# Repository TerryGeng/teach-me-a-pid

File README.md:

# teach-me-a-pid
Simplified schematic of a PID controller

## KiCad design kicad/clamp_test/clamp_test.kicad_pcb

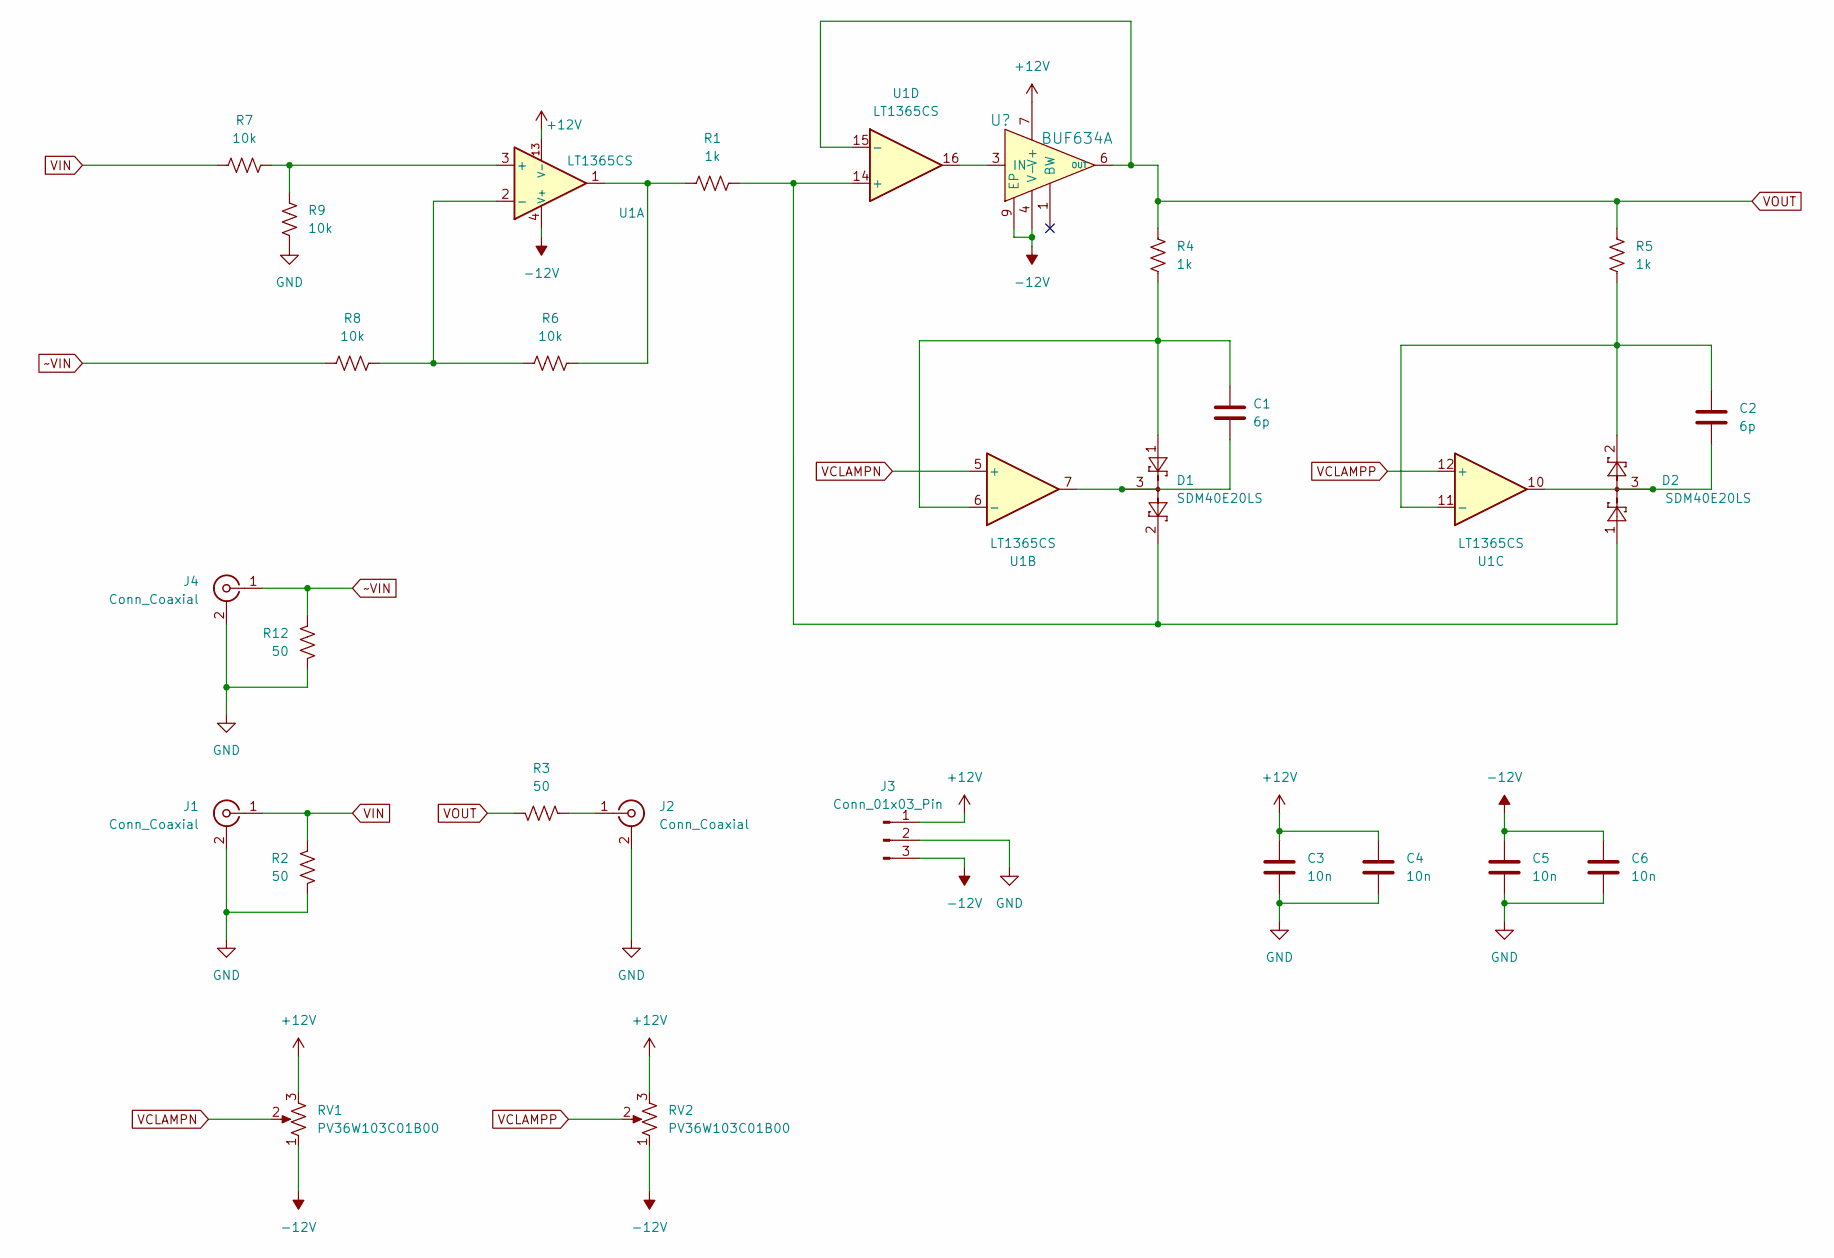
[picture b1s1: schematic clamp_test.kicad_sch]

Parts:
C1, C2: 6p; C_0603_1608Metric
C3, C4, C5, C6: 10n; C_0603_1608Metric
D1, D2: SDM40E20LS; SOT-23
J1, J2, J4: Conn_Coaxial; SMA_Amphenol_132291_Vertical
J3: Conn_01x03_Pin; PinHeader_1x03_P2.54mm_Vertical
R1, R4, R5: 1k; R_0603_1608Metric
R2, R3, R12: 50; R_0603_1608Metric
R6, R7, R8, R9: 10k; R_0603_1608Metric
RV1, RV2: PV36W103C01B00; Potentiometer_Bourns_3296W_Vertical
U1: LT1365CS; SOIC-16_3.9x9.9mm_P1.27mm
U2: BUF634A; TI_SO-PowerPAD-8_ThermalVias; PARTNO BUF634AIDDAR; DIGIKEY 296-BUF634AIDDARCT-ND

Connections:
+12V: C3.1, C4.1, J3.1, RV1.3, RV2.3, U1.13 (V-), U2.7 (V+)
-12V: C5.1, C6.1, J3.3, RV1.1, RV2.1, U1.4 (V+), U2.4 (V-), U2.9 (EP)
GND: C3.2, C4.2, C5.2, C6.2, J1.2 (Ext), J2.2 (Ext), J3.2, J4.2 (Ext), R2.2, R9.2, R12.2
unnamed: C1.2, D1.3, U1.7
unnamed: C2.2, D2.3, U1.10
unnamed: J2.1 (In), R3.2
unnamed: R1.1, R6.1, U1.1
unnamed: R7.1, R9.1, U1.3 (+)
unnamed: R6.2, R8.1, U1.2 (-)
unnamed: C1.1, D1.1, R4.1, U1.6 (-)
unnamed: C2.1, D2.2, R5.1, U1.11 (-)
unnamed: D1.2, D2.1, R1.2, U1.14 (+)
unnamed: U1.16, U2.3 (IN)
VCLAMPN: RV1.2, U1.5 (+)
VCLAMPP: RV2.2, U1.12 (+)
VIN: J1.1 (In), R2.1, R7.2
VOUT: R3.1, R4.2, R5.2, U1.15 (-), U2.6 (OUT)
~VIN: J4.1 (In), R8.2, R12.1

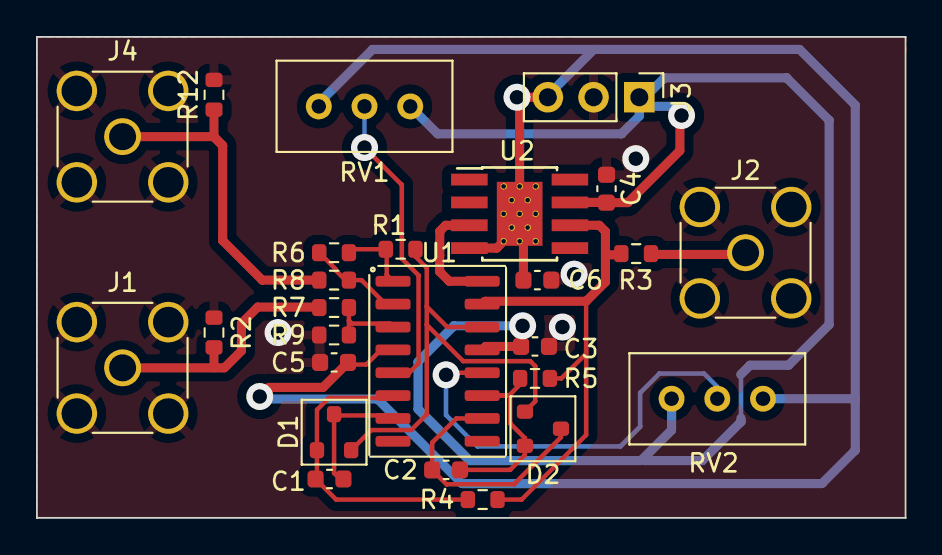
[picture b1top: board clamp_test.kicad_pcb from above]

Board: 2 copper layers, 48.3 x 26.7 mm, 26 parts (0 on the bottom side), 18 nets.

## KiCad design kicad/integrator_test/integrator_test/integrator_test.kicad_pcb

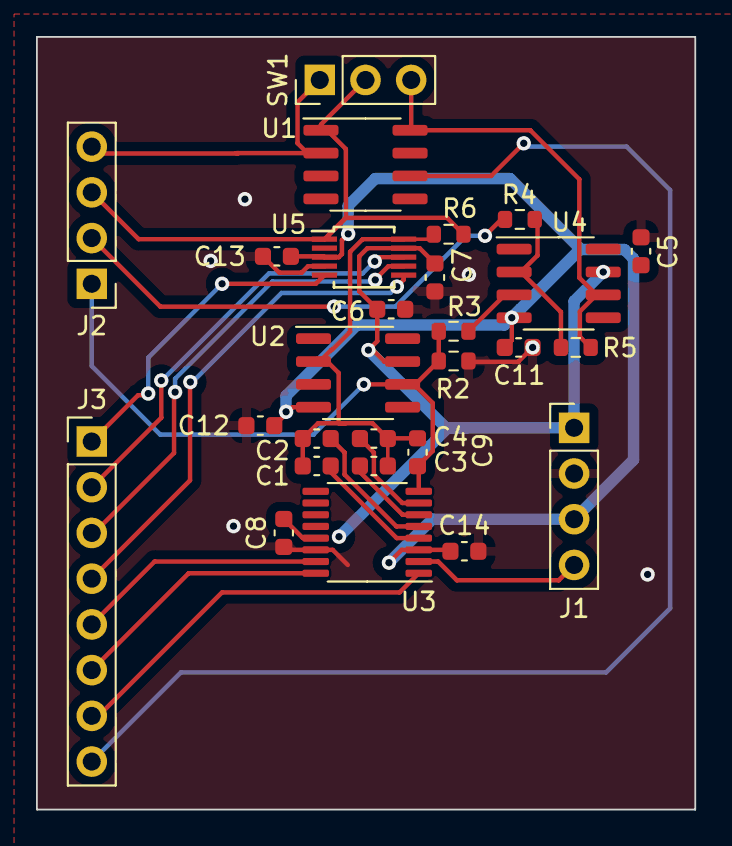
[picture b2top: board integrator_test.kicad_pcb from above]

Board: 2 copper layers, 36.6 x 42.9 mm, 27 parts (0 on the bottom side), 24 nets.

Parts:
C1: 1nF; C_0603_1608Metric
C2: 10nF; C_0603_1608Metric
C3, C5, C6, C7, C8, C11, C12, C13, C14: 100nF; C_0603_1608Metric
C4: 1uF; C_0603_1608Metric
C9: DNP; C_0603_1608Metric
J1, J2: Conn_01x04_Pin; PinHeader_1x04_P2.54mm_Vertical
J3: Conn_01x08_Pin; PinHeader_1x08_P2.54mm_Vertical
R2, R4: 1k; R_0603_1608Metric
R3, R5: 4.8k; R_0603_1608Metric
R6: DNP; R_0603_1608Metric
SW1: SW_SPDT; PinHeader_1x03_P2.54mm_Vertical
U1: DG419DY-T1-E3; SOIC-8_3.9x4.9mm_P1.27mm
U2, U4: OPA189; SOIC-8_3.9x4.9mm_P1.27mm
U3: DG408DQ-T1-E3; TSSOP-16_4.4x5mm_P0.65mm
U5: AD5290; MSOP-10_3x3mm_P0.5mm

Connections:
+3V3: J1.4, U3.2 (EN)
+12V: C5.1, C6.1, C7.1, C8.1, J1.1, U2.7 (V+), U3.13 (VDD), U4.7 (V+), U5.9 (Vdd+)
-12V: C11.1, C12.1, C13.1, C14.1, J1.3, U2.4 (V-), U3.3 (VSS), U4.4 (V-), U5.3 (Vss-)
GND: C5.2, C6.2, C7.2, C8.2, C11.2, C12.2, C13.2, C14.2, J1.2, R2.1, U2.3 (+), U3.14 (GND), U5.4 (GND)
INT_CAP_SEL_A0: J3.7, U3.1 (A0)
INT_CAP_SEL_A1: J3.6, U3.16 (A1)
INT_CAP_SEL_A2: J3.5, U3.15 (A2)
INT_R+: J2.3, R6.1, SW1.2 (B), U1.1, U5.1 (RH)
INT_R-: C1.1, C2.1, C3.1, C4.1, C9.1, R6.2, U2.2 (-), U5.10 (RW)
I_IN: J2.4, SW1.1 (A), U1.2
I_OUT: C9.2, J2.1, R2.2, R3.1, U2.6, U3.8 (D)
I_OVERRIDE: J2.2, R4.1
I_OVERRIDE_EN: J3.8, U1.6
unnamed: R5.2, SW1.3 (C), U1.8, U4.6
unnamed: C1.2, U3.4 (S1)
unnamed: C2.2, U3.5 (S2)
unnamed: C3.2, U3.6 (S3)
unnamed: C4.2, U3.7 (S4)
unnamed: R3.2, U4.3 (+)
unnamed: R4.2, R5.1, U4.2 (-)
R_CLK: J3.4, U5.6 (CLK)
R_CS: J3.1, U5.5 (~CS)
R_SDI: J3.3, U5.7 (SDI)
R_SDO: J3.2, U5.8 (SDO)

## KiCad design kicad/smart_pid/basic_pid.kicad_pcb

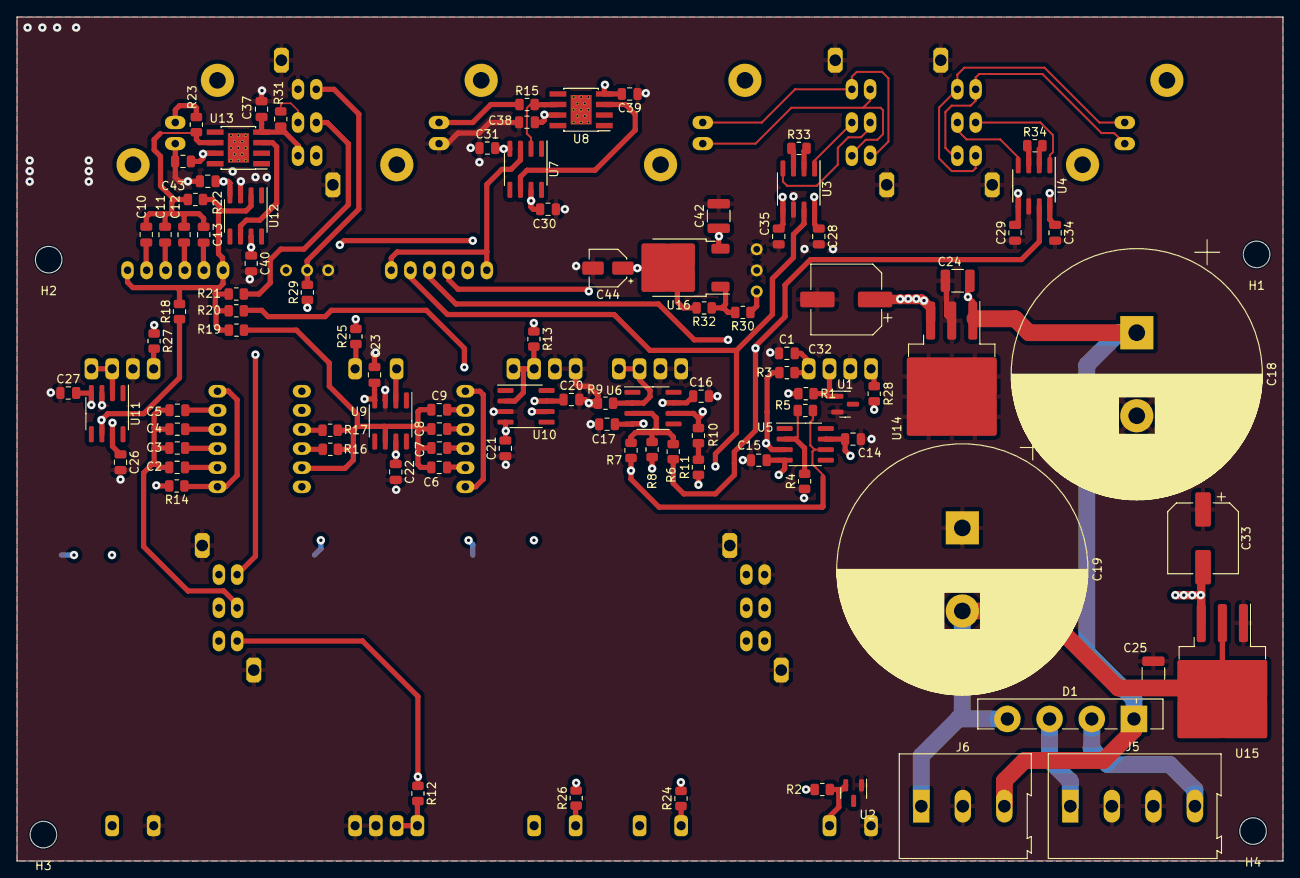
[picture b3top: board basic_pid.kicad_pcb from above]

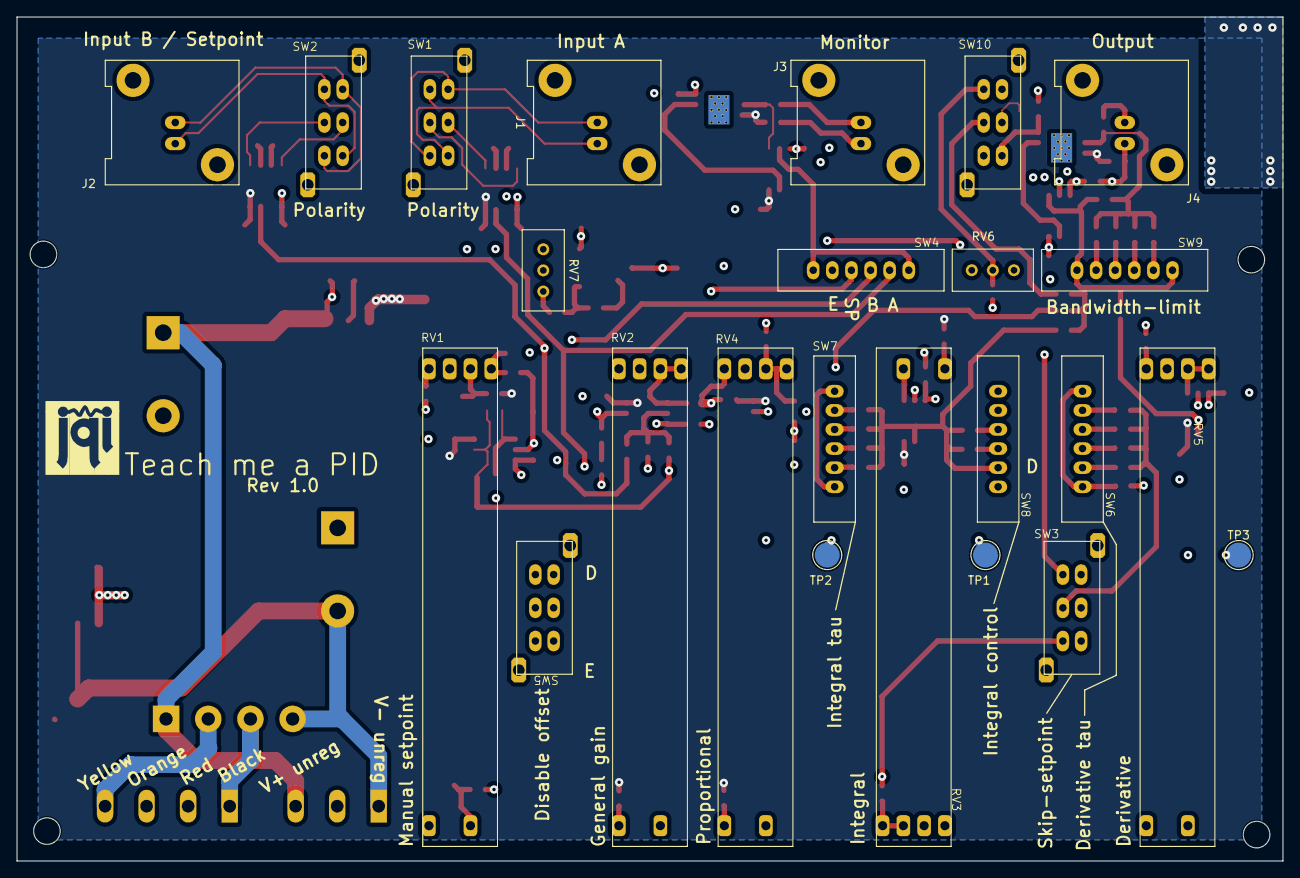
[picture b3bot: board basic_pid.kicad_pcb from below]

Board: 4 copper layers, 152.4 x 101.6 mm, 125 parts (25 on the bottom side), 74 nets.

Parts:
C1: 100n; C_0805_2012Metric
C2, C10: DNP; C_0805_2012Metric
C3, C11: 100p; C_0805_2012Metric
C4, C12: 1n; C_0805_2012Metric
C5, C13: 10n; C_0805_2012Metric
C6: 1nF; C_0805_2012Metric
C7: 10nF; C_0805_2012Metric
C8, C14, C15, C16, C17, C20, C21, C22, C23, C26, C27, C28, C29, C30, C31, C34, C35, C36, C37, C38, C39, C40, C43: 100nF; C_0805_2012Metric
C9: 1uF; C_0805_2012Metric
C18, C19: 22mF; CP_Radial_D30.0mm_P10.00mm_SnapIn
C24, C25, C42: 10uF; C_1210_3225Metric
C32, C33: 220uF; CP_Elec_8x6.9
C44: 22uF; CP_Elec_4x5.8
D1: GBU4A; Diode_Bridge_Vishay_GBU
H1, H2, H3, H4: MountingHole; MountingHole_3.2mm_M3_ISO14580
J1: Input A; BNC_Amphenol_031-5539_Vertical
J2: Input B / Setpoint; BNC_Amphenol_031-5539_Vertical
J3: Monitor; BNC_Amphenol_031-5539_Vertical
J4: Output; BNC_Amphenol_031-5539_Vertical
J5: Screw_Terminal_01x04; TerminalBlock_Altech_AK300-4_P5.00mm
J6: Screw_Terminal_01x03; TerminalBlock_Altech_AK300-3_P5.00mm
LOGO3: JQI-LOGOSILK; JQI_LOGO_NEGATIVE-SILKSCREEN
R1, R2: R_US; R_0805_2012Metric
R3, R4, R5, R6, R7, R8, R9, R10, R11, R12, R13, R18, R19, R20, R21, R22: 10k; R_0805_2012Metric
R14: 220; R_0805_2012Metric
R15, R23: 50; R_0805_2012Metric
R16: 1M; R_0805_2012Metric
R17: 10M; R_0805_2012Metric
R24, R25, R26, R27, R28, R30, R31: 1k; R_0805_2012Metric
R29, R33, R34: DNP; R_0805_2012Metric
R32: 330; R_0805_2012Metric
RV1, RV2, RV3, RV4, RV5: 100k; Slide_pot_45mm
RV6: 10K; Potentiometer_Bourns_3296W_Vertical
RV7: 2k; Potentiometer_Bourns_3296W_Vertical
SW1, SW2, SW3, SW5, SW10: SW_DPDT_x2; MHS222
SW4, SW6, SW7, SW8, SW9: SW_SP4T; SLB1470
TP1, TP2, TP3: TestPoint; TestPoint_Pad_D3.0mm
U1, U2: LM4040DBZ-5; SOT-23
U3, U4: INA849; SOIC-8_3.9x4.9mm_P1.27mm
U5, U6, U7, U9, U10, U11, U12: OPA189; SOIC-8_3.9x4.9mm_P1.27mm
U8, U13: BUF634A; TI_SO-PowerPAD-8_ThermalVias
U14: LM2940CS-12/NOPB; TO-263-3_TabPin2
U15: LM2990SX-12; TO-263-3_TabPin2
U16: LM317_TO-252; TO-252-2

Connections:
+12V: C14.1, C16.1, C20.1, C22.1, C26.1, C28.1, C30.1, C32.1, C34.1, C36.1, C38.1, R1.2, R24.2, R25.2, R26.2, U3.8 (Vs+), U4.8 (Vs+), U5.7 (V+), U6.7 (V+), U7.7 (V+), U8.7 (V+), U9.7 (V+), U10.7 (V+), U11.7 (V+), U13.7 (V+), U14.3 (VO)
-12V: C15.2, C17.2, C21.2, C23.2, C27.2, C29.2, C31.2, C33.2, C35.2, C37.2, C39.2, R2.1, R27.1, R28.1, R29.1, R31.1, RV6.3, SW10.4 (A), U3.5 (Vs-), U4.5 (Vs-), U5.4 (V-), U6.4 (V-), U7.4 (V-), U8.4 (V-), U8.9 (EP), U9.4 (V-), U10.4 (V-), U11.4 (V-), U13.4 (V-), U13.9 (EP), U15.3 (OUT)
/Supply_and_filtering/black: D1.3, J5.1
/Supply_and_filtering/yellow: D1.2, J5.4
Error_signal: R10.2, R12.1, R13.1, SW3.1 (A), SW4.4, U6.6
GND: C1.1, C14.2, C15.1, C16.2, C17.1, C18.2, C19.1, C20.2, C21.1, C22.2, C23.1, C24.2, C25.1, C26.2, C27.1, C28.2, C29.1, C30.2, C31.1, C32.2, C33.1, C34.2, C35.1, C36.2, C37.1, C38.2, C39.1, C40.2, C42.2, C43.2, C44.2, J3.2 (Ext), J4.2 (Ext), J5.2, J5.3, J6.2, R4.1, R9.1, RV1.A, RV1.L (Dummy), RV2.C, RV2.L (Dummy), RV3.C, RV3.L (Dummy), RV4.C, RV4.L (Dummy), RV5.A, RV5.L (Dummy), RV6.1, RV7.2, RV7.3, SW1.S, SW2.S, SW3.S, SW5.3 (C), SW5.S, SW10.6 (C), SW10.S, U1.2 (A), U2.1 (K), U3.6 (Ref), U4.6 (Ref), U9.3 (+), U10.3 (+), U11.3 (+), U12.3 (+), U14.2 (GND), U15.1 (GND)
Input_A: R8.1, SW3.3 (C), SW4.1, U3.7
Input_B: R6.1, SW4.2, U4.7
Internal_setpoint: R5.2, R7.1, SW4.3, U5.6
unnamed: C1.2, R3.1, RV1.2
unnamed: C2.2, SW6.1
unnamed: C3.2, SW6.2
unnamed: C4.2, SW6.3
unnamed: C5.2, SW6.4
unnamed: C6.1, C7.1, C8.1, C9.1, R16.2, R17.2, R19.1, SW8.1, TP1.1, U9.6
unnamed: C6.2, SW7.1
unnamed: C7.2, SW7.2
unnamed: C8.2, SW7.3
unnamed: C9.2, SW7.4
unnamed: C10.2, SW9.1
unnamed: C11.2, SW9.2
unnamed: C12.2, SW9.3
unnamed: C13.2, SW9.4
unnamed: J1.2 (Ext), SW1.3 (C), SW1.4 (A)
unnamed: J1.1 (In), SW1.1 (A), SW1.6 (C)
unnamed: J2.2 (Ext), SW2.3 (C), SW2.4 (A)
unnamed: J2.1 (In), SW2.1 (A), SW2.6 (C)
unnamed: J3.1 (In), R15.2
unnamed: J4.1 (In), R23.2
unnamed: R10.1, R11.2
unnamed: R11.1, RV2.3
unnamed: R12.2, RV3.1, RV3.2
unnamed: R16.1, SW8.2
unnamed: R17.1, SW8.3
unnamed: R18.1, RV5.3, TP3.1, U11.6
unnamed: R20.1, RV4.3, TP2.1, U10.6
unnamed: R24.1, RV2.A
unnamed: R25.1, RV3.A
unnamed: R26.1, RV4.A
unnamed: R27.2, RV5.C
unnamed: R28.2, RV1.C
unnamed: R30.1, RV7.1
unnamed: R33.1, U3.3 (Rg)
unnamed: R33.2, U3.2 (Rg)
unnamed: R34.1, U4.3 (Rg)
unnamed: R34.2, U4.2 (Rg)
unnamed: SW1.2 (B), U3.1 (-)
unnamed: SW1.5 (B), U3.4 (+)
unnamed: SW2.2 (B), U4.1 (-)
unnamed: SW2.5 (B), U4.4 (+)
unnamed: C2.1, C3.1, C4.1, C5.1, SW3.2 (B)
unnamed: SW4.C (Common), U7.3 (+)
unnamed: R3.2, SW5.2 (B), U5.3 (+)
unnamed: R14.1, SW6.C (Common)
unnamed: RV3.3, SW7.C (Common), SW8.C (Common), U9.2 (-)
unnamed: R18.2, R19.2, R20.2, R21.1, R22.1, SW9.C (Common), U12.2 (-)
unnamed: R29.2, RV6.2, SW10.3 (C)
unnamed: R1.1, RV1.1, U1.1 (K)
unnamed: R2.2, RV1.3, U2.2 (A)
unnamed: R4.2, R5.1, U5.2 (-)
unnamed: R6.2, R7.2, R8.2, U6.3 (+)
unnamed: R9.2, RV2.1, RV2.2, U6.2 (-)
unnamed: R15.1, U7.2 (-), U8.6 (OUT)
unnamed: U7.6, U8.3 (IN)
unnamed: R13.2, RV4.1, RV4.2, U10.2 (-)
unnamed: R14.2, RV5.1, RV5.2, U11.2 (-)
unnamed: U12.6, U13.3 (IN)
unnamed: C10.1, C11.1, C12.1, C13.1, R22.2, R23.1, U13.6 (OUT)
unnamed: R30.2, R32.1, U16.1 (ADJ)
Positive_offset: R21.2, SW10.2 (B)
V+_unreg: C18.1, C24.1, C42.1, D1.1 (+), J6.3, U14.1 (VI), U16.3 (VI)
V-_unreg: C19.2, C25.2, D1.4 (-), J6.1, U15.2 (IN)
Vlim+: C40.1, C44.1, R32.2, U12.7 (V+), U16.2 (VO)
Vlim-: C43.1, R31.2, SW10.5 (B), U12.4 (V-)

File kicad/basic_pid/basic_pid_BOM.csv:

#,Reference,Qty,Value,Footprint,DNP,DIGIKEY,PARTNO
1,C1,1,100n,Capacitor_SMD:C_0805_2012Metric,,,
2,"C2, C10",2,DNP,Capacitor_SMD:C_0805_2012Metric,,,
3,"C3, C11",2,100p,Capacitor_SMD:C_0805_2012Metric,,,
4,"C4, C12",2,1n,Capacitor_SMD:C_0805_2012Metric,,,
5,"C5, C13",2,10n,Capacitor_SMD:C_0805_2012Metric,,,
6,C6,1,1nF,Capacitor_SMD:C_0805_2012Metric,,,
7,C7,1,10nF,Capacitor_SMD:C_0805_2012Metric,,,
8,"C8, C14, C15, C16, C17, C20, C21, C22, C23, C26, C27, C28, C29, C30, C31, C34, C35, C36, C37, C38, C39, C40, C43",23,100nF,Capacitor_SMD:C_0805_2012Metric,,,
9,C9,1,1uF,Capacitor_SMD:C_0805_2012Metric,,,
10,"C18, C19",2,22mF,Capacitor_THT:CP_Radial_D30.0mm_P10.00mm_SnapIn,,338-2433-ND,380LX223M035K052
11,"C24, C25, C42",3,10uF,Capacitor_SMD:C_1210_3225Metric,,,
12,"C32, C33",2,220uF,Capacitor_SMD:CP_Elec_8x6.9,,PCE3955CT-ND,EEE-1VA221UP
13,C44,1,22uF,Capacitor_SMD:CP_Elec_4x5.8,,493-14929-1-ND,UCM1V220MCL1GS
14,D1,1,GBU4A,Diode_THT:Diode_Bridge_Vishay_GBU,,GBU4A-ND,GBU4A
15,"H1, H2, H3, H4",4,MountingHole,MountingHole:MountingHole_3.2mm_M3_ISO14580,,,
16,J1,1,Input A,lib:BNC_Amphenol_031-5539_Vertical,,,
17,J2,1,Input B / Setpoint,lib:BNC_Amphenol_031-5539_Vertical,,,
18,J3,1,Monitor,lib:BNC_Amphenol_031-5539_Vertical,,,
19,J4,1,Output,lib:BNC_Amphenol_031-5539_Vertical,,,
20,J5,1,Screw_Terminal_01x04,TerminalBlock:TerminalBlock_Altech_AK300-4_P5.00mm,,,
21,J6,1,Screw_Terminal_01x03,TerminalBlock:TerminalBlock_Altech_AK300-3_P5.00mm,,,
22,"R1, R2",2,R_US,Resistor_SMD:R_0805_2012Metric,,,
23,"R3, R4, R5, R6, R7, R8, R9, R10, R11, R12, R13, R18, R19, R20, R21, R22",16,10k,Resistor_SMD:R_0805_2012Metric,,2019-RN73H2ATTD1002B25CT-ND,
24,R14,1,220,Resistor_SMD:R_0805_2012Metric,,,
25,"R15, R23",2,50,Resistor_SMD:R_0805_2012Metric,,,
26,R16,1,1M,Resistor_SMD:R_0805_2012Metric,,YAG3766CT-ND,AC0805JR-071ML
27,R17,1,10M,Resistor_SMD:R_0805_2012Metric,,311-10MARCT-ND,RC0805JR-0710ML
28,"R24, R25, R26, R27, R28, R30, R31",7,1k,Resistor_SMD:R_0805_2012Metric,,,
29,R29,1,DNP,Resistor_SMD:R_0805_2012Metric,,,
30,R32,1,330,Resistor_SMD:R_0805_2012Metric,,,
31,"R33, R34",2,DNP,Resistor_SMD:R_0805_2012Metric,,2019-RN73H2ATTD1002B25CT-ND,
32,"RV1, RV2, RV3, RV4, RV5",5,100k,lib:Slide_pot_45mm,,PTL45-15O0-104B1-ND,PTL45-15O0-104B1
33,RV6,1,10K,Potentiometer_THT:Potentiometer_Bourns_3296W_Vertical,,118-3296W-1-103RLFCT-ND,3296W-1-103RLF
34,RV7,1,2k,Potentiometer_THT:Potentiometer_Bourns_3296W_Vertical,,3296Y-202LF-ND,3296Y-1-202LF
35,"SW1, SW2, SW3, SW5, SW10",5,SW_DPDT_x2,lib:MHS222,,450-1572-ND,1825289-1
36,"SW4, SW6, SW7, SW8, SW9",5,SW_SP4T,lib:SLB1470,,679-2621-ND,SLB1470
37,"TP1, TP2, TP3",3,TestPoint,TestPoint:TestPoint_Pad_D3.0mm,,,
38,"U1, U2",2,LM4040DBZ-5,Package_TO_SOT_SMD:SOT-23,,LM4040B50FTADICT-ND,LM4040B50FTA
39,"U3, U4",2,INA849,Package_SO:SOIC-8_3.9x4.9mm_P1.27mm,,,
40,"U5, U6, U7, U9, U10, U11, U12",7,OPA189,Package_SO:SOIC-8_3.9x4.9mm_P1.27mm,,296-47522-ND,OPA189ID
41,"U8, U13",2,BUF634A,lib:TI_SO-PowerPAD-8_ThermalVias,,296-BUF634AIDDARCT-ND,BUF634AIDDAR
42,U14,1,LM2940CS-12/NOPB,Package_TO_SOT_SMD:TO-263-3_TabPin2,,LM2940CS-12/NOPB-ND,LM2940CS-12/NOPB
43,U15,1,LM2990SX-12,Package_TO_SOT_SMD:TO-263-3_TabPin2,,LM2990SX-12/NOPBCT-ND,LM2990SX-12/NOPB
44,U16,1,LM317_TO-252,Package_TO_SOT_SMD:TO-252-2,,497-1574-1-ND,LM317MDT-TR

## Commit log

2023-06-27 Schematic made.
    TO DO:
    1) Figure out the values for all components to provide a suitable
    2) design the power supply and filtering section.
    3) Find suitable potentiometers and switches: I like the idea of sliders! (they occupy space however!)
    4) Find a suitable footprint for the capacitor socket: maybe a zif?
2023-07-01 Schematic almost finalized:
    Ended up using switches to select pre-set capacitors rather than ZIFs
    TO DO:
    1) design the power supply and filtering section.
    2) Layout work (consider adding capacitors for stabilization...)
2023-07-06 last partial schematic using OPA189 everywhere
2023-07-07 Schematic finalized and layout work begun
2023-07-11 Layout almost completed
    This is an almost completed snapshot of the layout. Here what to do:
    1) Make sure that when flipped the back has sliders on the bottom: this will require
    reversing the direction of increasing gain with consequent shortening of certain
    signal traces
    2) Fix the position of connectors, sliders and switches to "reasonable locations"
    3) Make a verbose silkscreen (expecially on bottom) showing all functions.
2023-07-13 Board is functionally operational but requires more reviews:
    TO DO list
    1) Substitute input op-amps with an INA849: that should give higher bandwidth
    2) Make sure that when flipped the back has sliders on the bottom: this will require
    reversing the direction of increasing gain with consequent shortening of certain
    signal traces
    3) Fix the position of connectors, sliders and switches to "reasonable locations"
2023-07-24 version sent to Advanced Circuits and OSHStencils
2023-09-28 smart pid schematics
2023-09-29 Added inverter and modified ext. setpoint disable
2023-10-02 added integrator test board
2023-10-09 integrator test board v2
2023-10-10 Optimzied some traces for the integrator test board
2023-11-14 Clamp test board: first version
2023-11-15 Clamp test board: removed unused vias
2023-11-16 Changed buffer position
2023-11-17 adjusted layout
